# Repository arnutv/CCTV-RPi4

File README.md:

# CCTV-RPi4

A complete, self-hosted DIY CCTV system using **6 ESP32-CAM modules** and a **Raspberry Pi 4 or 5** as a local WiFi hub, recorder and dashboard. No cloud, no subscriptions, no router required.

---

## What it does

- **6 wireless cameras** stream MJPEG to a local Raspberry Pi
- **Motion detection** on each ESP32-CAM triggers recording (saves to RPi storage **and** each camera's local SD card simultaneously)
- **Web dashboard** accessible from any phone or laptop — 3×2 live grid, click any camera to enlarge
- **HDMI monitor** mode — Pi shows a fullscreen 3×2 grid directly on a TV (Chromium kiosk on RPi ≥ 2 GB, native pygame on RPi 1 GB)
- **Solar-powered cameras** — each camera runs on a 6V/10W panel + 2× 18650 batteries (~$27 hardware)
- **3D-printed enclosure** — parametric OpenSCAD & FreeCAD designs included
- **Adaptive install** — one script auto-detects RAM and configures the system optimally (LITE / MID / FULL modes)
- **Optional internet bridge** — `connect_router.sh` lets the RPi share your home WiFi or ethernet with the cameras

---

## Architecture

```
   ┌──────────────┐   ┌──────────────┐   ┌──────────────┐
   │ ESP32-CAM #1 │   │ ESP32-CAM #2 │   │ ESP32-CAM #N │
   │  + SD card   │   │  + SD card   │   │  + SD card   │
   │  + solar/bat │   │  + solar/bat │   │  + solar/bat │
   └──────┬───────┘   └──────┬───────┘   └──────┬───────┘
          │ MJPEG @ port 81  │                  │
          │ + frame uploads  │                  │
          └─────────┬────────┴──────────────────┘
                    │  WiFi 192.168.4.0/24 (WPA2)
                    ▼
         ┌──────────────────────────┐
         │   Raspberry Pi 4 or 5    │
         │   wlan0 = AP (.4.1)      │
         │   Flask server :8080     │
         │   ├─ /         dashboard │
         │   ├─ /display  HDMI grid │
         │   ├─ /upload   from cams │
         │   └─ /api/cameras …      │
         └──┬──────────────────┬────┘
            │ HDMI             │ optional eth0 / wlan1
            ▼                  ▼
        ┌──────┐          ┌──────────────┐
        │  TV  │          │  Home router │
        └──────┘          │  → Internet  │
                          └──────────────┘
```

---

## Hardware

### Per camera (6× total)

| Item | Spec | ~Cost |
|---|---|---|
| AI-Thinker ESP32-CAM | OV2640 sensor, ESP32-S | $8 |
| MicroSD card | 16-32 GB Class 10 | $8 |
| 6 V 10 W solar panel | 250×200 mm | $9 |
| CN3791 MPPT charger | 1S Li-ion output | $3 |
| 2× 18650 Li-ion | Samsung 30Q or similar (3000 mAh) | $8 |
| 1S BMS module | DW01A+FS8205A, 20×10 mm (over-discharge + short-circuit) | $1 |
| MT3608 boost converter | 5 V output | $1 |
| IP65 junction box | 158×90×65 mm | $6 |
| Misc (PG7 gland, lens disc, screws) | | ~$3 |
| **Subtotal per camera** | | **~$47** |

### Hub

| Item | Spec | ~Cost |
|---|---|---|
| Raspberry Pi 4 (1 GB+) or RPi 5 (2 GB+) | | $35-50 |
| Power supply | 5V/3A USB-C (Pi 4) or 5V/5A (Pi 5) | $8-13 |
| MicroSD (or USB SSD) | 32 GB+ for OS + recordings | $8 |
| Active cooler | RPi 5 only | $5 |
| micro-HDMI cable | optional, for TV display | $5 |

**Total system cost: ~$330 for 6 cameras + hub.**

---

## Quick start

### 1. Raspberry Pi setup (15 min)

Flash **Raspberry Pi OS 64-bit (Bookworm)** to your SD card with Raspberry Pi Imager. Set hostname, enable SSH, configure your wifi for first-time access.

SSH in and run:

```bash
git clone https://github.com/arnutv/CCTV-RPi4.git
cd CCTV-RPi4/rpi4
sudo bash install.sh
sudo reboot
```

The installer **auto-detects** your board and RAM, then chooses:

| Mode | Trigger | What runs |
|---|---|---|
| **LITE** | RAM < 1.5 GB | Headless, native pygame HDMI display, `gpu_mem=32` |
| **MID** | RAM 1.5-3 GB | Chromium kiosk (trimmed), `gpu_mem=64` |
| **FULL** | RAM ≥ 4 GB | Full Chromium kiosk, `gpu_mem=128` |

After reboot:
- WiFi network **`CCTV_Network`** (pass: `cctv1234!!`) — cameras join this
- Dashboard at **`http://192.168.4.1:8080/`** from phone or laptop
- HDMI shows the 3×2 grid automatically (if connected)

### 2. Flash the cameras (5 min each)

For each ESP32-CAM, edit `CCTV-Camera/cam_config.h` to set its ID and name:

```cpp
#define CAM_ID   1                  // 1-6, unique per camera
#define CAM_NAME "Front Door"       // shown in dashboard
```

Open `CCTV-Camera/CCTV-Camera.ino` in Arduino IDE:
- Board: **AI Thinker ESP32-CAM**
- ESP32 core: **1.0.6** (pinned for stability)
- Partition: **Huge APP (3MB No OTA / 1MB SPIFFS)**

Flash with a USB-to-serial adapter (GPIO0 to GND while pressing reset).

> **Tip:** the included [GitHub Actions workflow](.github/workflows/build-firmware.yml) builds the firmware in the cloud — no Arduino IDE needed. Just go to the Actions tab → "Build ESP32-CAM Firmware" → Run workflow, fill in the cam ID/name, and download the `.bin` from the artifacts.

### 3. Power & mount the cameras

Connect each camera to its solar panel + 18650 battery rig (see `enclosure/wiring.txt`). Power on — the camera auto-connects to `CCTV_Network`, gets its static IP (`192.168.4.10X` based on `CAM_ID`), and appears live on the dashboard.

---

## Web dashboard

Browse to `http://192.168.4.1:8080/` from any device on the CCTV WiFi:

- **3×2 live grid** of all cameras with status pills (LIVE / MOTION / OFFLINE)
- **Click any camera** to enlarge to a large modal with live feed, battery %, and snapshot/page buttons
- **Recordings browser** with per-camera tabs, frame-by-frame playback, save individual frames
- **Storage chips** show RPi disk free + estimated days of retention left + auto-cleanup setting
- **One-click cleanup** button to flush recordings older than the retention period (default 30 days)
- **System health** in the header: CPU temp, uptime, internet IP (if connected), disk bar

---

## HDMI display

Plug an HDMI monitor or TV into the RPi (micro-HDMI to HDMI cable for RPi 4/5).

| Mode | Renderer | RAM cost | Notes |
|---|---|---|---|
| **LITE** | `display.py` — pygame on KMSDRM | ~80 MB | Auto-installed by `install.sh` on 1 GB boards; no X server, no browser |
| **MID/FULL** | Chromium kiosk → `/display` | ~500 MB | Same look as the web dashboard, GPU-accelerated |

Exit display: `Esc` or `Q` on a keyboard, or `sudo systemctl stop cctv-display`.

---

## Optional: internet bridge

By default the RPi is an island — cameras can talk to it but not to the internet. To bridge:

```bash
# Via ethernet (cleanest)
sudo bash rpi4/connect_router.sh eth

# Via USB WiFi dongle
sudo bash rpi4/connect_router.sh wifi "HomeWiFi" "yourpassword"

# Undo
sudo bash rpi4/connect_router.sh --remove
```

Now the dashboard is also reachable from your home network (look for the IP in the dashboard header), and you can SSH in from anywhere on your LAN.

---

## Enclosure & 3D printing

Files in `enclosure/` — two formats, each part also has its own standalone file:

| File | Contents |
|---|---|
| `tray.scad` | Electronics tray — open, F6, export STL |
| `solar_bracket.scad` | Solar panel arm — open, F6, export STL |
| `cctv_enclosure.scad` | Both parts in one file (`PART = "all"` preview) |
| `cctv_enclosure.FCMacro` | FreeCAD Python macro — same 2 parts |

Designed to drop inside a **140 × 78 mm outer IP65 junction box** (typical thai weatherproof box). The lens hole and ESP32-CAM mount are drilled directly through the box's own lid.

Parts (3D-printed):

| Part | File | Print time | Filament | Purpose |
|---|---|---|---|---|
| Electronics tray | `tray.scad` | 90 min | 28 g | Holds battery + MPPT + boost inside the IP65 box |
| Solar bracket | `solar_bracket.scad` | 55 min | 20 g | L-arm screws to wall (2× M5); solar panel bolts to far end of arm (4× M4) |

**Print in PETG** (or ASA) at 0.2 mm, 4 perimeters, 25 % gyroid infill. No supports needed.

See `enclosure/wiring.txt` for the full assembly + waterproofing checklist.

---

## File layout

```
CCTV-RPi4/
├── CCTV-Camera/                 # Arduino sketch (flash this to each ESP32-CAM)
│   ├── CCTV-Camera.ino
│   ├── cam_config.h            # ← Edit CAM_ID and CAM_NAME per unit
│   ├── camera_pins.h
│   ├── motion.h
│   ├── power.h
│   ├── recorder.h
│   └── webui.h
├── rpi4/                        # Raspberry Pi server side
│   ├── install.sh              # One-shot setup (auto-adaptive LITE/MID/FULL)
│   ├── cctv_server.py          # Flask dashboard + upload endpoint
│   ├── display.py              # Native pygame HDMI display (LITE mode)
│   └── connect_router.sh       # Optional internet bridge
├── preview/                     # Browser preview of the dashboard (Windows PC)
│   ├── index.html              # Static mock dashboard
│   └── serve.ps1               # Tiny PowerShell HTTP server
├── enclosure/                   # 3D-printable parts
│   ├── tray.scad               # Electronics tray — standalone, open → F6 → STL
│   ├── solar_bracket.scad      # Solar panel arm  — standalone, open → F6 → STL
│   ├── cctv_enclosure.scad     # Combined preview (both parts, PART variable)
│   ├── cctv_enclosure.FCMacro  # FreeCAD Python macro (same 2 parts)
│   └── wiring.txt              # ASCII wiring + waterproofing notes
├── .github/workflows/
│   └── build-firmware.yml      # Cloud-builds ESP32 firmware, exports .bin
├── .gitignore
└── README.md
```

---

## Configuration cheatsheet

| What | Where | Default |
|---|---|---|
| WiFi SSID + password | `CCTV-Camera/cam_config.h` + `rpi4/install.sh` | `CCTV_Network` / `cctv1234!!` |
| Camera ID + name | `CCTV-Camera/cam_config.h` per unit | `CAM_ID 1`, `"Front Door"` |
| RPi static IP for AP | `rpi4/install.sh` | `192.168.4.1` |
| Recording retention | `rpi4/cctv_server.py` → `RETENTION_DAYS` | `30` days |
| Frame resolution | inside `CCTV-Camera.ino`: `s->set_framesize()` | `FRAMESIZE_VGA` |
| GPU memory | auto via install.sh | 32/64/128 MB |
| Server port | `rpi4/cctv_server.py` | `8080` |
| Cameras list (for dashboard) | `rpi4/cctv_server.py` → `CAMERAS` | 6 entries, edit to add/remove |

---

## Performance

Measured with **6 cameras at VGA 5 FPS, motion-triggered recording**:

| Board | Boot | CPU idle | CPU peak | RAM used | Smoothness |
|---|---|---|---|---|---|
| RPi 4 1 GB | ~25 s | 4 % | 35-45 % | ~600 MB | Adequate |
| RPi 4 2/4/8 GB | ~22 s | 3 % | 25-35 % | ~600 MB | Smooth |
| RPi 5 (2/4/8 GB) | ~12 s | 1-2 % | 12-18 % | ~700 MB | Snappy |

Cameras can scale up to **~12 units** before grid cells become too small to read on a 32" TV.

---

## Troubleshooting

| Symptom | Likely cause | Fix |
|---|---|---|
| Camera shows OFFLINE in dashboard | Bad wifi / wrong CAM_ID | Re-flash with correct config; check serial output |
| Dashboard slow / laggy | Too many concurrent viewers | Max 2-3 phones streaming full grid; close extras |
| Recordings folder filling disk | Retention too long | Lower `RETENTION_DAYS` and run "Clean now" |
| HDMI black on RPi 5 1 GB | Chromium ran out of memory | Confirm install picked LITE mode; check `systemctl status cctv-display` |
| Solar camera dies overnight | Cloudy days drained battery | Upsize to 12 V 20 W panel + LiFePO4 (see `wiring.txt` "Robust tier") |
| Lens fogged from inside | Trapped condensation | Add a PTFE breathable vent on the bottom of the IP65 box |

---

## Contributing

PRs welcome. Run the cloud build (Actions tab) before opening a PR to confirm the firmware still compiles.

---

## License

MIT — see [LICENSE](LICENSE) if present, otherwise consider this MIT-licensed.

---

## Credits

Built with `esp32-arduino`, `esp_camera`, `Flask`, `pygame`, `hostapd`, `dnsmasq` and a Raspberry Pi.

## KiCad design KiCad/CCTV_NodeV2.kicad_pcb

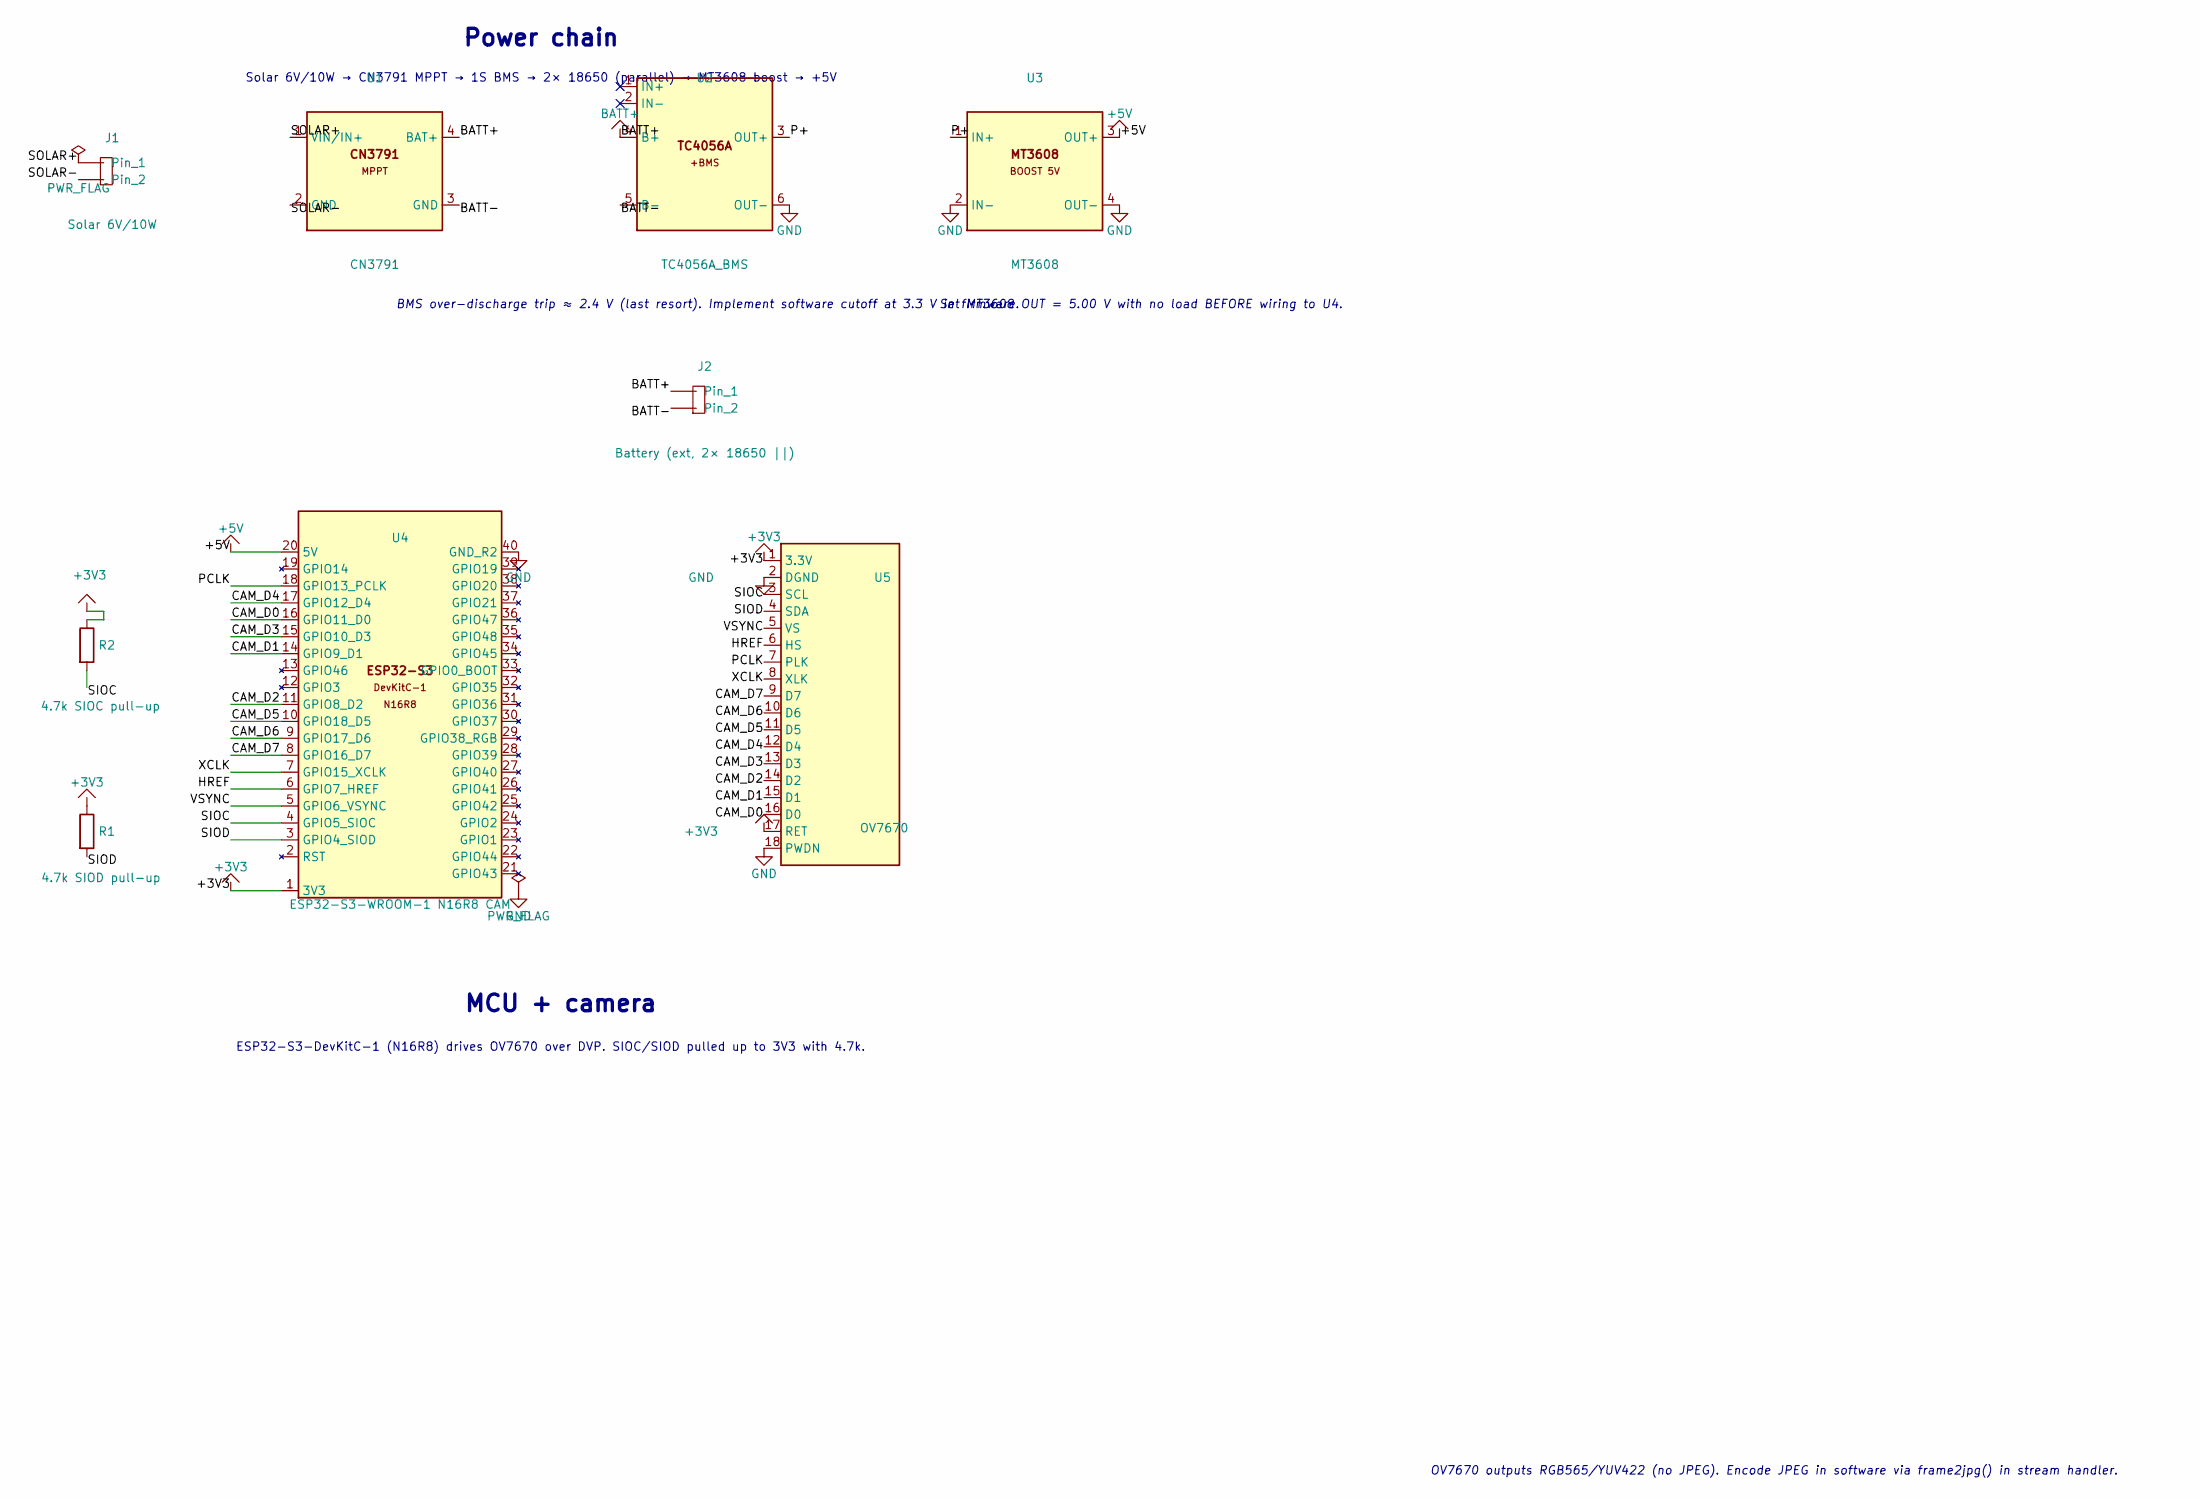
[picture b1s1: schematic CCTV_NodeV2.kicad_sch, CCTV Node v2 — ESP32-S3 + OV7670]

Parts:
J1: Solar 6V/10W; PinHeader_1x02_P2.54mm_Vertical
J2: Battery (ext, 2× 18650 ||); PinHeader_1x02_P2.54mm_Vertical
R1: 4.7k SIOD pull-up; R_Axial_DIN0207_L6.3mm_D2.5mm_P7.62mm_Horizontal
R2: 4.7k SIOC pull-up; R_Axial_DIN0207_L6.3mm_D2.5mm_P7.62mm_Horizontal
U1: CN3791; CN3791_Module
U2: TC4056A_BMS; TC4056A_BMS_Module
U3: MT3608; MT3608_Module
U4: ESP32-S3-WROOM-1 N16R8 CAM; ESP32-S3-CAM-N16R8_2x20_P2.54mm
U5: OV7670; OV7670_Module

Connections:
+3V3: R1.1, R2.1, U4.1 (3V3_1), U5.1 (3V3), U5.17 (RESET)
+5V: U3.3 (OUT+), U4.20 (5V_21)
/BATT-: J2.2, U1.3 (GND), U2.5 (B-)
/CAM_D0: U4.16 (GPIO11_D0_17), U5.16 (D0)
/CAM_D1: U4.14 (GPIO9_D1_15), U5.15 (D1)
/CAM_D2: U4.11 (GPIO8_D2_12), U5.14 (D2)
/CAM_D3: U4.15 (GPIO10_D3_16), U5.13 (D3)
/CAM_D4: U4.17 (GPIO12_D4_18), U5.12 (D4)
/CAM_D5: U4.10 (GPIO18_D5_11), U5.11 (D5)
/CAM_D6: U4.9 (GPIO17_D6_10), U5.10 (D6)
/CAM_D7: U4.8 (GPIO16_D7_9), U5.9 (D7)
/HREF: U4.6 (GPIO7_HREF_7), U5.6 (HREF)
/P+: U2.3 (OUT+), U3.1 (IN+)
/PCLK: U4.18 (GPIO13_PCLK_19), U5.7 (PCLK)
/SIOC: R2.2, U4.4 (GPIO5_SIOC_5), U5.3 (SIOC)
/SIOD: R1.2, U4.3 (GPIO4_SIOD_4), U5.4 (SIOD)
/SOLAR+: J1.1, U1.1 (VIN/IN+)
/SOLAR-: J1.2, U1.2 (GND)
/VSYNC: U4.5 (GPIO6_VSYNC_6), U5.5 (VSYNC)
/XCLK: U4.7 (GPIO15_XCLK_8), U5.8 (XCLK)
BATT+: J2.1, U1.4 (BAT+), U2.4 (B+)

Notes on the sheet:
Power chain
Solar 6V/10W → CN3791 MPPT → 1S BMS → 2× 18650 (parallel) → MT3608 boost → +5V
MCU + camera
ESP32-S3-DevKitC-1 (N16R8) drives OV7670 over DVP. SIOC/SIOD pulled up to 3V3 with 4.7k.
Set MT3608 OUT = 5.00 V with no load BEFORE wiring to U4.
BMS over-discharge trip ≈ 2.4 V (last resort). Implement software cutoff at 3.3 V in firmware.
OV7670 outputs RGB565/YUV422 (no JPEG). Encode JPEG in software via frame2jpg() in stream handler.

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
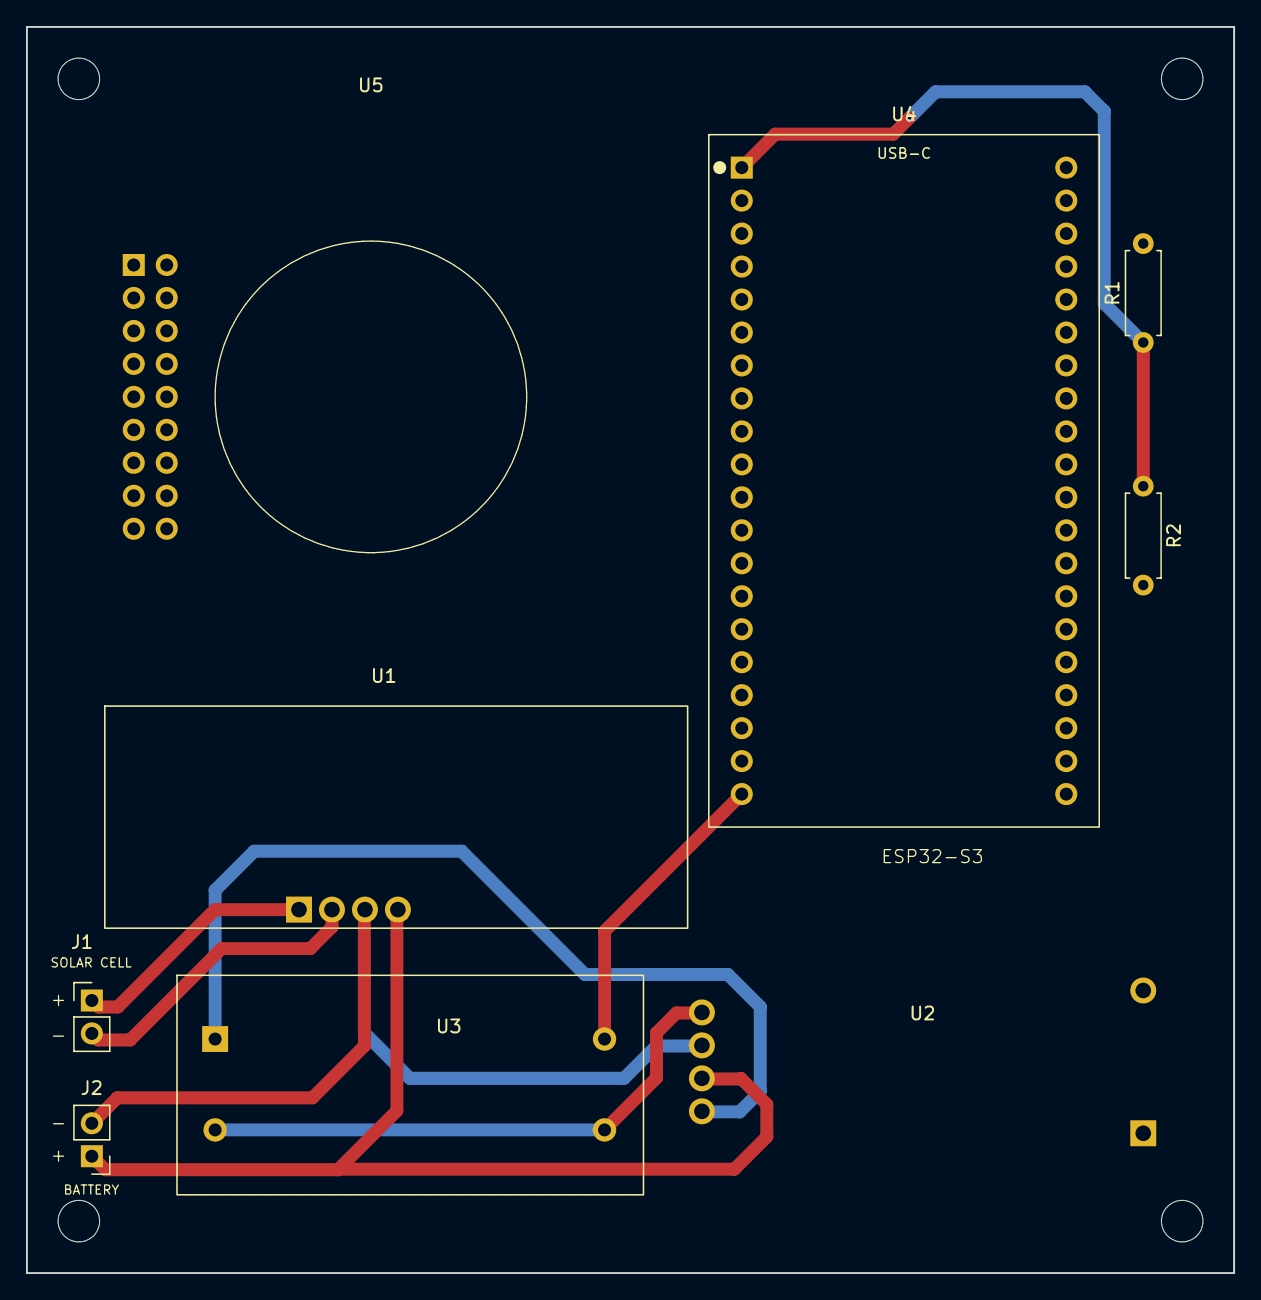
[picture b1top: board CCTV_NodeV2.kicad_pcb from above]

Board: 2 copper layers, 93.0 x 96.0 mm, 9 parts (0 on the bottom side), 23 nets.

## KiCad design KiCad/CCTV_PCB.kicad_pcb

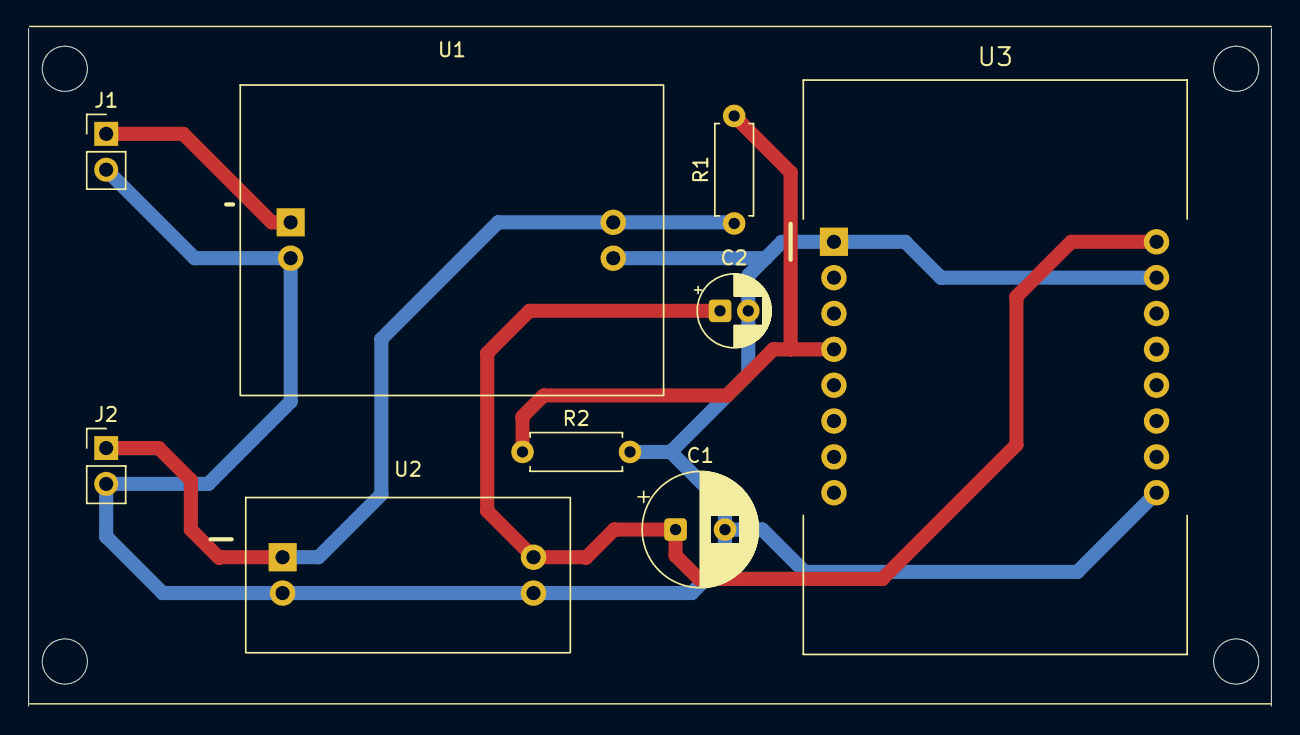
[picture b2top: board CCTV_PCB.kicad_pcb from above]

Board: 2 copper layers, 88.1 x 48.0 mm, 9 parts (0 on the bottom side), 5 nets.

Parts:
C1: 100uF_10V; CP_Radial_D8.0mm_P3.50mm
C2: 10uF_10V; CP_Radial_D5.0mm_P2.00mm
J1: Solar_Input; PinHeader_1x02_P2.54mm_Vertical
J2: Battery_Conn; PinHeader_1x02_P2.54mm_Vertical
R1, R2: 100k; R_Axial_DIN0207_L6.3mm_D2.5mm_P7.62mm_Horizontal
U1: CN3791_Module
U2: MT3608_Module
U3: ESP32-CAM; ESP32-CAM_AI-Thinker

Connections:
+5V: C1.1, C2.1, U2.3, U3.9
BATT+: J2.1, R1.1, U1.3, U2.1
GND: C1.2, C2.2, J1.2, J2.2, R2.2, U1.2, U1.4, U2.2, U2.4, U3.1, U3.10, U3.16
SENSE: R1.2, R2.1, U3.4
SOLAR+: J1.1, U1.1

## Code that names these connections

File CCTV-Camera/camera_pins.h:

#pragma once
#include "esp_camera.h"

// AI-Thinker ESP32-CAM pin map
#define PWDN_GPIO_NUM   32
#define RESET_GPIO_NUM  -1
#define XCLK_GPIO_NUM    0
#define SIOD_GPIO_NUM   26
#define SIOC_GPIO_NUM   27
#define Y9_GPIO_NUM     35
#define Y8_GPIO_NUM     34
#define Y7_GPIO_NUM     39
#define Y6_GPIO_NUM     36
#define Y5_GPIO_NUM     21
#define Y4_GPIO_NUM     19
#define Y3_GPIO_NUM     18
#define Y2_GPIO_NUM      5
#define VSYNC_GPIO_NUM  25
#define HREF_GPIO_NUM   23
#define PCLK_GPIO_NUM   22

inline camera_config_t getCameraConfig() {
  camera_config_t c;
  memset(&c, 0, sizeof(c));
  c.ledc_channel = LEDC_CHANNEL_0;
  c.ledc_timer   = LEDC_TIMER_0;
  c.pin_d0       = Y2_GPIO_NUM;  c.pin_d1 = Y3_GPIO_NUM;
  c.pin_d2       = Y4_GPIO_NUM;  c.pin_d3 = Y5_GPIO_NUM;
  c.pin_d4       = Y6_GPIO_NUM;  c.pin_d5 = Y7_GPIO_NUM;
  c.pin_d6       = Y8_GPIO_NUM;  c.pin_d7 = Y9_GPIO_NUM;
  c.pin_xclk     = XCLK_GPIO_NUM;
  c.pin_pclk     = PCLK_GPIO_NUM;
  c.pin_vsync    = VSYNC_GPIO_NUM;
  c.pin_href     = HREF_GPIO_NUM;
  c.pin_sscb_sda = SIOD_GPIO_NUM;
  c.pin_sscb_scl = SIOC_GPIO_NUM;
  c.pin_pwdn     = PWDN_GPIO_NUM;
  c.pin_reset    = RESET_GPIO_NUM;
  c.xclk_freq_hz = 20000000;
  c.pixel_format = PIXFORMAT_JPEG;
  c.frame_size   = FRAMESIZE_VGA;   // 640×480 — RPi 4 handles this easily
  c.jpeg_quality = 10;              // 0–63, lower = better
  c.fb_count     = 2;
  return c;
}

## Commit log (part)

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2026-05-22 Initial commit: 6-camera CCTV system with adaptive RPi 4/5 support
    Components:
    - ESP32-CAM firmware (Arduino) with MJPEG streaming, motion detection,
    dual storage (RPi upload + SD card backup) for 6 cameras
    - RPi Flask server (cctv_server.py) with web dashboard, recordings browser,
    cleanup scheduler, retention estimator, /api/cameras endpoint
    - Adaptive install.sh: auto-detects RAM and picks LITE/MID/FULL mode,
2026-05-22 Resize default box parameters for 140x78 mm outer junction box
    Changed BOX_W from 148 to 134 (inner), BOX_D from 80 to 72 (inner),
    BOX_H from 55 to 50 to suit a typical 140x78 mm outer thai junction box
    (3 mm walls assumed).
    Verified component fit:
    - Battery + MPPT + boost max footprint: 124.8 x 49.8 mm
    - Fits in new 134 x 72 mm inner area with 9.2 / 22.2 mm margins
2026-05-22 Remove tray_cover, camera_bezel, lid_seal — keep only 3 essential parts
    Slim down the printed parts list to just what's needed when you have a
    commercial IP65 junction box on hand:
    - electronics_tray — organises battery + MPPT + boost inside the box
    - solar_bracket — L-bracket for the solar panel
    - wall_mount — ball-joint articulating mount
    Removed:
2026-06-01 Add KiCad schematics/PCBs, footprint library, and parts list
    - CCTV_PCB and CCTV_Power KiCad projects (schematic + layout + backups)
    - CCTV_RPi4.pretty: custom footprints (ESP32-CAM, MT3608, CN3791, 18650 holder)
    - DRC report, autoroute scripts, fp-lib-table
    - รายการอุปกรณ์ ESP32-CAM CCTV.docx: parts list
    - Ignore KiCad/.history/ (auto-snapshots with their own .git)
2026-06-01 Assign footprints to CCTV_NodeV2 schematic + add 3 new module footprints
    New custom footprints in CCTV_RPi4.pretty/:
    - ESP32-S3-DevKitC-1.kicad_mod (17 thru-hole pads, 25.4x26mm body)
    - OV7670_Module.kicad_mod (18-pin 2x9 header, 24x24mm body with lens marker)
    - BMS_1S_DW01A_FS8205A.kicad_mod (4 thru-hole pads, 20x10mm body)
    Footprint assignments in CCTV_NodeV2.kicad_sch:
    - J1 Solar -> Connector_PinHeader_2.54mm:PinHeader_1x02_P2.54mm_Vertical
2026-06-01 Make J2 an external battery connector; route MT3608 from BMS P- (protected)
    - J2 footprint: BatteryHolder_18650 -> PinHeader_1x02 (battery now lives
    off-board, wired in via this 2-pin connector). Value updated to
    'Battery (ext, 2x 18650 ||)'.
    - Add net labels at BMS P+ (BATT+) and BMS P- (PROT-) — these were
    floating before, meaning the BMS protected output wasn't actually
    wired anywhere on the schematic.
2026-06-01 Add CCTV_NodeV2.kicad_pcb (placement-only) + Freerouting guide
    PCB:
    - 2-layer board, 100x80mm, A4 paper
    - 21 nets defined (SOLAR+/-, BATT+/-, GND, +5V, +3V3, SIOC, SIOD,
    VSYNC, HREF, PCLK, XCLK, CAM_D0..D7)
    - 9 components placed:
    J1 Solar 2-pin (10,12) | U1 CN3791 (35,12) | U2 BMS (62,12)
2026-06-01 Route CAM_D0..D3 on B.Cu (data lines 0-3 of camera bus)
    Each line uses 5 segments on B.Cu (back copper) so they cross
    underneath the existing F.Cu power and control traces without
    conflict. All traces 0.7mm width.
    Pattern per line: U4 right pad -> exit east -> south to bottom rail
    in the y=68-71 area -> east past OV7670 right edge -> north up to
    target y -> west into U5 right pad.
2026-06-01 Update routing guide: all 21 nets now fully routed (96 segments)
2026-06-01 Expand U4 ESP32-S3-DevKitC-1 schematic symbol from 17 to 44 pins
    All 44 physical pins are now present in the schematic symbol:
    - Pins 1-17: functional connections (unchanged, all nets stay wired)
    - Pins 18-31: NC right column (14 no_connect pins filling the right
    column above and below the D0-D7 data bus rows)
    - Pins 32-44: NC left column (13 no_connect pins filling the left
    column above pin 9/XCLK, the gap at y=5.08, and below pin 1/5V)
2026-06-01 Fix OV7670 pin numbering to match actual module (zigzag order)
    Previous versions used arbitrary sequential numbering that did NOT
    match the real OV7670 module. Corrected based on hardware datasheet.
    Correct pinout (2x9 zigzag, L=left col odd, R=right col even):
    Pin 1 (L) = SIOC Pin 2 (R) = SIOD
    Pin 3 (L) = VSYNC Pin 4 (R) = HREF
    Pin 5 (L) = PCLK Pin 6 (R) = XCLK
2026-06-01 Fix ESP32-S3-DevKitC-1 layout to match physical board (OceanLabz pinout)
    Footprint (ESP32-S3-DevKitC-1.kicad_mod):
    44 pads at correct physical y-positions (2.54mm pitch, y=-27.94 to +25.40)
    Left col pads 1-22 (x=-11.43):
    1=3V3, 2=3V3, 3=RST, 4=GPIO4, 5=GPIO5, 6=GPIO6, 7=GPIO7,
    8=GPIO15, 9=GPIO16, 10=GPIO17, 11=GPIO18, 12=GPIO8, 13=GPIO3,
    14=GPIO46, 15=GPIO9, 16=GPIO10, 17=GPIO11, 18=GPIO12, 19=GPIO13,
2026-06-01 Fix BMS → MT3608 power path: add P+ net, remove BATT+ bypass
    The MT3608 boost converter was incorrectly connected directly to the
    BATT+ net (raw battery positive), bypassing the 1S BMS protection.
    Correct power flow (battery → BMS → MT3608 → 5V → ESP32):
    Battery J2 + → BATT+ → BMS B+ (cell side, charging via CN3791)
    BMS P+ output → P+ → MT3608 IN+ (protected, load side)
    BMS P- output → PROT- → MT3608 IN- (already correct)
2026-06-01 Redesign CN3791 footprint: single-row 4-hole + correct pinout
    Physical module has 4 holes in a single row (not 2x2), labelled
    left-to-right: VIN | GND | GND | BAT
    CN3791_Module.kicad_mod (footprint):
    - Changed from wide 2x2 layout (x=+-20mm) to single row
    - 4 pads at 2.54mm pitch: x = -3.81, -1.27, +1.27, +3.81, all y=0
    - PCB outline: 35x17mm body on F.Fab + F.SilkS
2026-06-01 Update CN3791_Module PCB outline to correct 45x20mm size
    Previous outline was 35x17mm (wrong estimate).
    Actual module: 45mm wide x 20mm tall.
    Changes to F.Fab / F.SilkS / F.CrtYd rectangles:
    Old: (-17.5, -8.5) to (+17.5, +8.5) = 35 x 17 mm
    New: (-22.5, -10) to (+22.5, +10) = 45 x 20 mm
    Courtyard:
2026-06-01 Update .gitignore for KiCad runtime files; sync kicad_pro
    .gitignore:
    - Add ~*.lck (KiCad file-lock files created while files are open)
    - Add *.kicad_prl (KiCad per-user local project preferences)
    - Add *-backups/ (KiCad auto-backup folders, e.g. CCTV_NodeV2-backups/)
    KiCad/CCTV_NodeV2.kicad_pro:
    - Sync project settings updated by KiCad 10 after opening the PCB
2026-06-02 Replace U2 BMS from DW01A+FS8205A to TC4056A_BMS_Module
    Replaces the standalone 1S BMS (DW01A + FS8205A) with the TC4056A
    combined USB charger + BMS protection module on U2.
    Schematic (CCTV_NodeV2.kicad_sch):
    - Added CCTV2:TC4056A_BMS lib symbol (6 pins):
    Pin 1 = IN+ (USB 5V charging input) → NC marker
    Pin 2 = IN- (USB GND) → GND symbol
2026-06-02 Fix U3 MT3608 pad 4 (OUT-): GND → PROT- (same node as pad 2 IN-)
    Pad 2 (IN-) and pad 4 (OUT-) of the MT3608 module are connected
    together on the module's internal copper pour — they are the SAME
    electrical node. Both must be on the PROT- net so the BMS can
    actually cut off the load when over-discharge occurs.
    Previously pad 4 was changed to GND in the last commit, which would
    have shorted the BMS protection FETs (PROT- → GND directly) and
2026-06-02 Redesign TC4056A footprint to match actual module (2+4 pad layout)
    Physical layout from image:
    LEFT edge : USB-C connector + 2 pads
    pad 1 = IN+ (top, square)
    pad 2 = IN- (bottom)
    RIGHT edge: 4 pads at 2.54mm pitch
    pad 3 = OUT+ (top)
2026-06-02 Move all wiring labels/power symbols with U4 and U5
    All net labels, power symbols (+5V, +3V3, GND) and R1/R2 pull-up
    resistors have been relocated to the correct new pin positions.
    Because the ESP32-S3 symbol was redesigned with physical pin ordering
    (44 pins, new y-coordinates per pin), labels could NOT simply shift
    by a fixed offset — each needed its own target y calculated as:
    new_y = placed_y(220) − symbol_pin_y
2026-06-02 Move R1/R2 pull-ups and labels outside U4 body
    R1 (SIOD 4.7k pull-up) and R2 (SIOC 4.7k pull-up) were positioned
    at x=50 and x=55 respectively, which falls inside U4's body outline
    (x=44.76–75.24). Shifted all related elements 30mm to the left:
    R1 centre : x=50 → x=20
    R1 ref/value : x=53 → x=23
    R1 +3V3 flag : x=50 → x=20
2026-06-02 Separate R1 and R2 vertically to prevent overlap
    Both resistors were at y=232 (same height, x=20 and x=25) — only
    5mm apart, causing heavy visual overlap in eeschema.
    R1 (SIOD 4.7k pull-up) moved: y=232 → y=244
    Centre : (20,232) → (20,244)
    Ref/Value : (23,232/235) → (23,244/247)
    +3V3 flag : (20,228.19) → (20,240.19)
2026-06-03 Fix unconnected U4 pin 17 (CAM_D0) — move label to wire endpoint
    The CAM_D0 label near U4 was at (57.15, 137.16) but the wire
    from U4 pin 17 ends at (58.73, 137.45) — a small gap causing
    ERC 'pin unconnected' error.
    Connection chain after fix:
    U4 pin 17 (GPIO11_D0) at (66.04, 137.16)
    → wire → (58.73, 137.45)
2026-06-03 Connect U5 OV7670 pin17 RESET to +3V3 and pin18 PWDN to GND
    Pins 17 (RESET) and 18 (PWDN) were unconnected, which causes the
    OV7670 sensor to behave unpredictably:
    - RESET floating → spurious resets or sensor stuck in reset
    - PWDN floating → sensor may enter power-down randomly
    Correct connections for normal operation:
    Pin 17 RESET (138.43, 144.78) → +3V3 (active-low reset, HIGH = run)
2026-06-03 Connect U4 right-column GND pins (23, 43, 44) to GND
    The ESP32-S3-DevKitC-1 has 4 GND pads total:
    Pin 22 (left col, y=124.46) — already connected via wire+symbol ✓
    Pin 23 (right col, y=177.80) — was unconnected ✗
    Pin 43 (right col, y=127.00) — was unconnected ✗
    Pin 44 (right col, y=124.46) — was unconnected ✗
    Added GND power symbols at all three right-column GND pin
2026-06-03 Change U4 GND pins 23/43/44 from no_connect to passive type
    Pins 23 (GND_R), 43 (GND_R2), 44 (GND_R3) on U4's right column
    were defined as 'no_connect' type, causing KiCad to draw X markers
    on those pins in eeschema even though they are now wired to GND.
    Changed pin type: no_connect → passive for:
    Pin 23 (at 17.78 -27.94 180) GND_R — top of right column
    Pin 43 (at 17.78 22.86 180) GND_R2 — near bottom
2026-06-03 Delete 3 stray GND symbols beside U1 and U2
    Removed floating GND power symbols that were sitting ~1.27mm
    below component pins which already had correct net labels.
    These could cause unintended net merges in KiCad ERC.
    Deleted:
    GND at (67.3, 76.35) — beside U1 CN3791 pin2 (SOLAR- label)
    GND at (117.3, 76.35) — beside U2 TC4056A left pins (BATT- label)
2026-06-03 Remove all silkscreen from U4 footprint except Reference designator
    Deleted all fp_text user pin-label items from F.SilkS on the
    ESP32-S3-DevKitC-1 footprint (44 items: IO2-IO48, 3V3, GND,
    5V0, RST, TX0, RX0, USB-C, BOOT, etc.).
    These labels were causing DRC warnings (text_height < 0.8mm min)
    and add no practical value to the physical silkscreen —
    they are too small to read on the PCB at 0.55mm.
2026-06-03 Remove U2 edge silkscreen (outline, notch lines, pin labels)
    Deleted from U2 (TC4056A BMS module) F.SilkS in the PCB:
    - fp_rect outline (26x17mm body boundary on silkscreen)
    - fp_line x2 (top-left corner orientation notches)
    - fp_text user x7 (IN+, IN-, OUT+, B+, B-, OUT-, pin-1 marker)
    Kept:
    - property Reference 'U2' on F.SilkS (assembly ID)
